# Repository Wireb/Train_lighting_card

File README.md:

### Induction refractory furnance supporting files

### licence 
Copyright (c) 2015 Peter Shabino

Permission is hereby granted, free of charge, to any person obtaining a copy of this hardware, software, and associated documentation files
(the "Product"), to deal in the Product without restriction, including without limitation the rights to use, copy, modify, merge, publish,
distribute, sublicense, and/or sell copies of the Product, and to permit persons to whom the Product is furnished to do so, subject to the
following conditions:

The above copyright notice and this permission notice shall be included in all copies or substantial portions of the Product.

THE PRODUCT IS PROVIDED "AS IS", WITHOUT WARRANTY OF ANY KIND, EXPRESS OR IMPLIED, INCLUDING BUT NOT LIMITED TO THE WARRANTIES OF
MERCHANTABILITY, FITNESS FOR A PARTICULAR PURPOSE AND NONINFRINGEMENT. IN NO EVENT SHALL THE AUTHORS OR COPYRIGHT HOLDERS BE LIABLE
FOR ANY CLAIM, DAMAGES OR OTHER LIABILITY, WHETHER IN AN ACTION OF CONTRACT, TORT OR OTHERWISE, ARISING FROM, OUT OF OR IN CONNECTION
WITH THE PRODUCT OR THE USE OR OTHER DEALINGS IN THE PRODUCT.

### What is it
The current generation of controller card supports up to 11 normal LED channels plus one "special"  one that supports driving a bi-polar output. On the input side the controller will run off 6V to 60V AC or DC. (note I have NOT test this full range. I have tested 9Vac to 20Vac with no issues) It also has 4 opto-isolated inputs that will respond to ~3V to 32V AC or DC that can be used to pick one of 16 pre-programmed states. 

Currently there are 7 selectable states:
* Headlights
* running lights
* left turn
* right turn
* break lights
* reverse lights
* light bar flashers 

Via the programing button any state, combination of states, or none can be chosen for each of the 16 combinations of the 4 inputs.

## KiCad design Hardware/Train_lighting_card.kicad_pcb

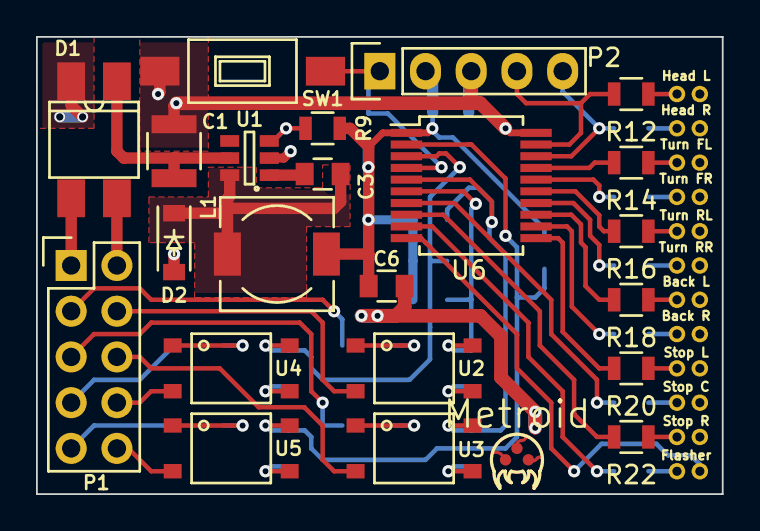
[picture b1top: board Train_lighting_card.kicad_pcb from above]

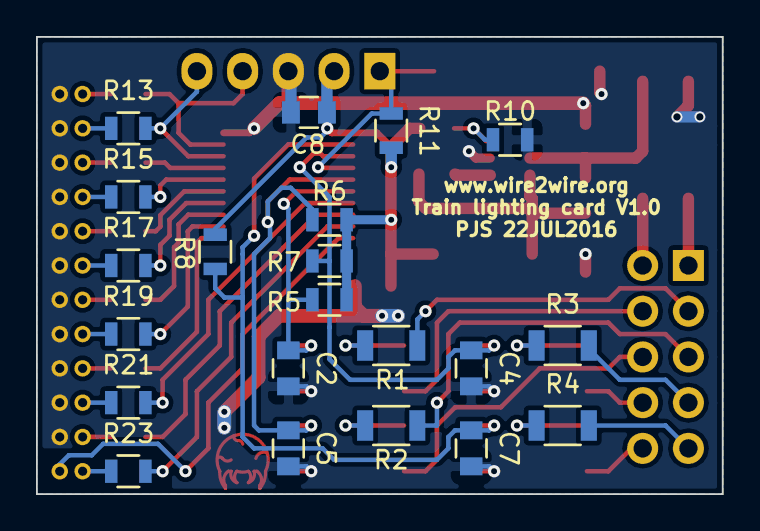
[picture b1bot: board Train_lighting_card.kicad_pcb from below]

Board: 2 copper layers, 38.1 x 25.4 mm, 56 parts (21 on the bottom side), 50 nets.

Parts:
C1: 3.3uF 100V; C_1210
C2, C4, C5, C7, C8: 0.1uF; C_0805
C3: 0.1uF 50V; C_0805
C6: 010uF 10V; C_0805
D1: MB6SCT-ND; SOIC-4
D2: PMEG6010CEH,115; SOD-123
L1: 68UH 900MA; Choke_SMD_6.3x6.3_H3
P1: CONN_01X10; Pin_Header_Straight_2x05
P2: CONN_01X05; Pin_Header_Straight_1x05
P3: Headlight L; wirepad_x2_20mil
P4: Headlight R; wirepad_x2_20mil
P5: Turn FL; wirepad_x2_20mil
P6: Turn FR; wirepad_x2_20mil
P7: Turn RL; wirepad_x2_20mil
P8: Turn RR; wirepad_x2_20mil
P9: Backup L; wirepad_x2_20mil
P10: Backup R; wirepad_x2_20mil
P11: Stop L; wirepad_x2_20mil
P12: Stop C; wirepad_x2_20mil
P13: Stop R; wirepad_x2_20mil
P14: Flashers; wirepad_x2_20mil
R1, R2, R3, R4: 820 Ohm; R_1206
R5, R6, R7, R8, R11: 100k Ohm; R_0805
R9: 36.0k Ohm; R_0805
R10: 6.49k Ohm; R_0805
R12, R13, R18, R19: 430 Ohm; R_0805
R14, R15, R16, R17, R20, R21, R22, R23: 150 Ohm; R_0805
SW1: SW_PUSH; SW_SPST_FSMSM
U1: LMR16006; SOT-23-6
U2, U3, U4, U5: LTV-354T; SOP-6-4
U6: PIC16F18344; SSOP-20_5.3x7.2mm_Pitch0.65mm
icon1: Metroid; metroid

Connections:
+5V: C6.1, C8.1, L1.2, P2.2, R5.2, R6.2, R7.2, R8.2, R9.2, R11.2, U6.1
GND: C1.2, C2.2, C4.2, C5.2, C6.2, C7.2, C8.2, D1.2, D2.2, P2.3, P3.2, P4.2, P5.2, P6.2, P7.2, P8.2, P9.2, P10.2, P11.2, P12.2, P13.2, R10.1, SW1.2, U1.2, U2.4, U3.4, U4.4, U5.4, U6.20
unnamed: C1.1, D1.1, U1.5
unnamed: C2.1, R5.1, U2.6, U6.6
unnamed: C3.1, D2.1, L1.1, U1.6
unnamed: C3.2, U1.1
unnamed: C4.1, R7.1, U4.6, U6.3
unnamed: C5.1, R6.1, U3.6, U6.5
unnamed: C7.1, R8.1, U5.6, U6.2
unnamed: D1.3, P1.1
unnamed: D1.4, P1.2
unnamed: P1.3, R1.2
unnamed: P1.4, U2.3
unnamed: P1.5, R2.2
unnamed: P1.6, U3.3
unnamed: P1.7, R3.2
unnamed: P1.8, U4.3
unnamed: P1.9, R4.2
unnamed: P1.10, U5.3
unnamed: P2.1, R11.1, SW1.1, U6.4
unnamed: P2.4, R12.2, U6.19
unnamed: P2.5, R13.2, U6.18
unnamed: P3.1, R12.1
unnamed: P4.1, R13.1
unnamed: P5.1, R14.1
unnamed: P6.1, R15.1
unnamed: P7.1, R16.1
unnamed: P8.1, R17.1
unnamed: P9.1, R18.1
unnamed: P10.1, R19.1
unnamed: P11.1, R20.1
unnamed: P12.1, R21.1
unnamed: P13.1, R22.1
unnamed: P14.1, R23.1
unnamed: P14.2, U6.10
unnamed: R1.1, U2.1
unnamed: R2.1, U3.1
unnamed: R3.1, U4.1
unnamed: R4.1, U5.1
unnamed: R9.1, R10.2, U1.3
unnamed: R14.2, U6.17
unnamed: R15.2, U6.16
unnamed: R16.2, U6.15
unnamed: R17.2, U6.14
unnamed: R18.2, U6.13
unnamed: R19.2, U6.12
unnamed: R20.2, U6.11
unnamed: R21.2, U6.7
unnamed: R22.2, U6.8
unnamed: R23.2, U6.9

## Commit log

2016-07-23 :space_invader: Added .gitattributes & .gitignore files
2016-07-23 First release
    First release of firmware and hardware designs
2016-07-23 added readme
2016-07-23 formatting changes
2016-07-23 formatting
